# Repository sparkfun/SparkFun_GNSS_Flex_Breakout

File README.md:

SparkFun GNSS Flex Breakout
========================================

[*SparkFun GNSS Flex Breakout (GPS-28962)*](https://www.sparkfun.com/sparkfun-gnss-flex-breakout.html)

The [SparkFun GNSS Flex breakout](https://www.sparkfun.com/sparkfun-gnss-flex-breakout.html) is a *carrier board* for our GNSS Flex modules. In its simplest form, the GNSS Flex Breakout board provides access to all of the interfaces from a GNSS Flex module.

- Need access to all those UART pins? The Breakout provides that.
- Want to communicate with the GNSS directly over USB? You can do that too, if the GNSS module supports USB.

The GNSS Flex Breakout comes populated with two sets of 2x10 pin, 2mm pitch male headers for attaching a GNSS Flex module. With these headers, the GNSS Flex system is designed to be modular so that boards are pin-compatible for upgrades and can be easily swapped for repairs. Depending on the capabilities of the GNSS Flex module that is connected, these pins will breakout the USB, UART (x4), I^2^C, and SD card interfaces for the GNSS receiver along with any PPS (x2) or event (x2) signals, using a standardized pin out.

By default, the CH342 USB-to-Serial converter chip is connected to both the GNSS `UART1` and `UART2` interfaces. When you connect the `UART` USB port to your computer and install the driver, those two UART interfaces will appear as COM ports. If you need dedicated access to the `UART1` or `UART2` breakout pins, or want to use either of the JST connectors, you will need to disable the CH342. On this board, we have made this simple; just pull the `CH342 EN` breakout pin `LOW` or connect it to `GND`. Otherwise, there is also a `CH342 EN` jumper you can solder instead.

We have also included two 6-pin JST connectors, same as the ones used on Pixhawk flight controllers. The JST connectors allow you to: connect the GNSS to a Pixhawk; or connect a radio to the GNSS to transfer (e.g.) RTCM correction data. There are four LEDs indicators for power to the board and the `PPS1`, `PVT`, and `RTK` signals from the GNSS Flex module. Power can be provided by any or all of: the USB connectors or the `VIN` breakout pin. By default, Pin 1 of the JST connectors provides 5V output. But jumpers on the board allow the voltage to be changed to 3.3V. Or you can isolate the other power sources and connect an external 5V power input on Pin 1 instead. It is up to you.

> [!IMPORTANT]
> Depending on the GNSS Flex module, this product will likely require an external antenna:
>
> - Be sure to check out the hookup guide for more information on the GNSS Flex module.
> - Users can also find [GNSS Antennas](https://www.sparkfun.com/gnss/gnss-antennas.html) in our catalog.
>
> Users will have two options for connecting an external GNSS antenna to their GNSS receiver.
>
> - The GNSS Flex modules will usually come with a U.FL connector for external antenna.
> - For a sturdier connection, an SMA connector is available on the SparkFun GNSS Flex Breakout that is bridged to an U.FL connector. Users simply need to jumper the U.FL connectors on both the SparkPNT GNSS Flex module and SparkFun GNSS Flex Breakout with a short U.FL cable.

Documentation
--------------
- **[Hookup Guide (mkdocs)](http://docs.sparkfun.com/SparkFun_GNSS_Flex_System/)** - A hookup guide for the entire ecosystem of SparkFun GNSS Flex carrier boards and SparkPNT GNSS Flex modules, hosted by GitHub pages.<br>

Repository Contents
-------------------
- **[/docs](/docs/)** - Online documentation files
  - [/assets](/docs/assets/) - Assets files
    - [/3d_model](/docs/assets/3d_model/) - Files for the 3D models
      - [/3D CAD Model](/docs/assets/3d_model/cad_model.step) (.step)
    - [/board_files](/docs/assets/board_files/) - Files for the product design
      - [KiCad Design Files](/docs/assets/board_files/kicad_files.zip) (.zip)
      - [Schematic](/docs/assets/board_files/schematic.pdf) (.pdf)
      - [Dimensions](/docs/assets/board_files/dimensions.pdf) (.pdf)
    - [/component_documentation](/docs/assets/component_documentation/) - Datasheets for hardware components
    - [/img/hookup_guide/](/docs/assets/img/hookup_guide/) - Images for hookup guide documentation
- **[/Hardware](/Hardware/)** - Hardware design files (.brd, .sch)
  - **[/Production](/Production/)** - Production files

Product Variants
----------------
GNSS Flex *Carrier* Boards:

- [GPS-28962](https://www.sparkfun.com/sparkfun-gnss-flex-breakout.html) - GNSS Flex Breakout
- [GPS-28137](https://www.sparkfun.com/sparkfun-gnss-flex-phat.html) - GNSS Flex pHAT

Version History
---------------
- [v10](https://github.com/sparkfun/SparkFun_GNSS_Flex_Breakout/releases/tag/v10) - Initial Release
- [v11](https://github.com/sparkfun/SparkFun_GNSS_Flex_Breakout/releases/tag/v11) - Refactored the 3D model for new color adjustment script

License Information
-------------------

This product is ***open source***!

Please review the [`LICENSE.md`](./LICENSE.md) file for license information.

If you have any questions or concerns about licensing, please contact technical support on our [SparkFun forums](https://forum.sparkfun.com/viewforum.php?f=152).

Distributed as-is; no warranty is given.

- Your friends at SparkFun.

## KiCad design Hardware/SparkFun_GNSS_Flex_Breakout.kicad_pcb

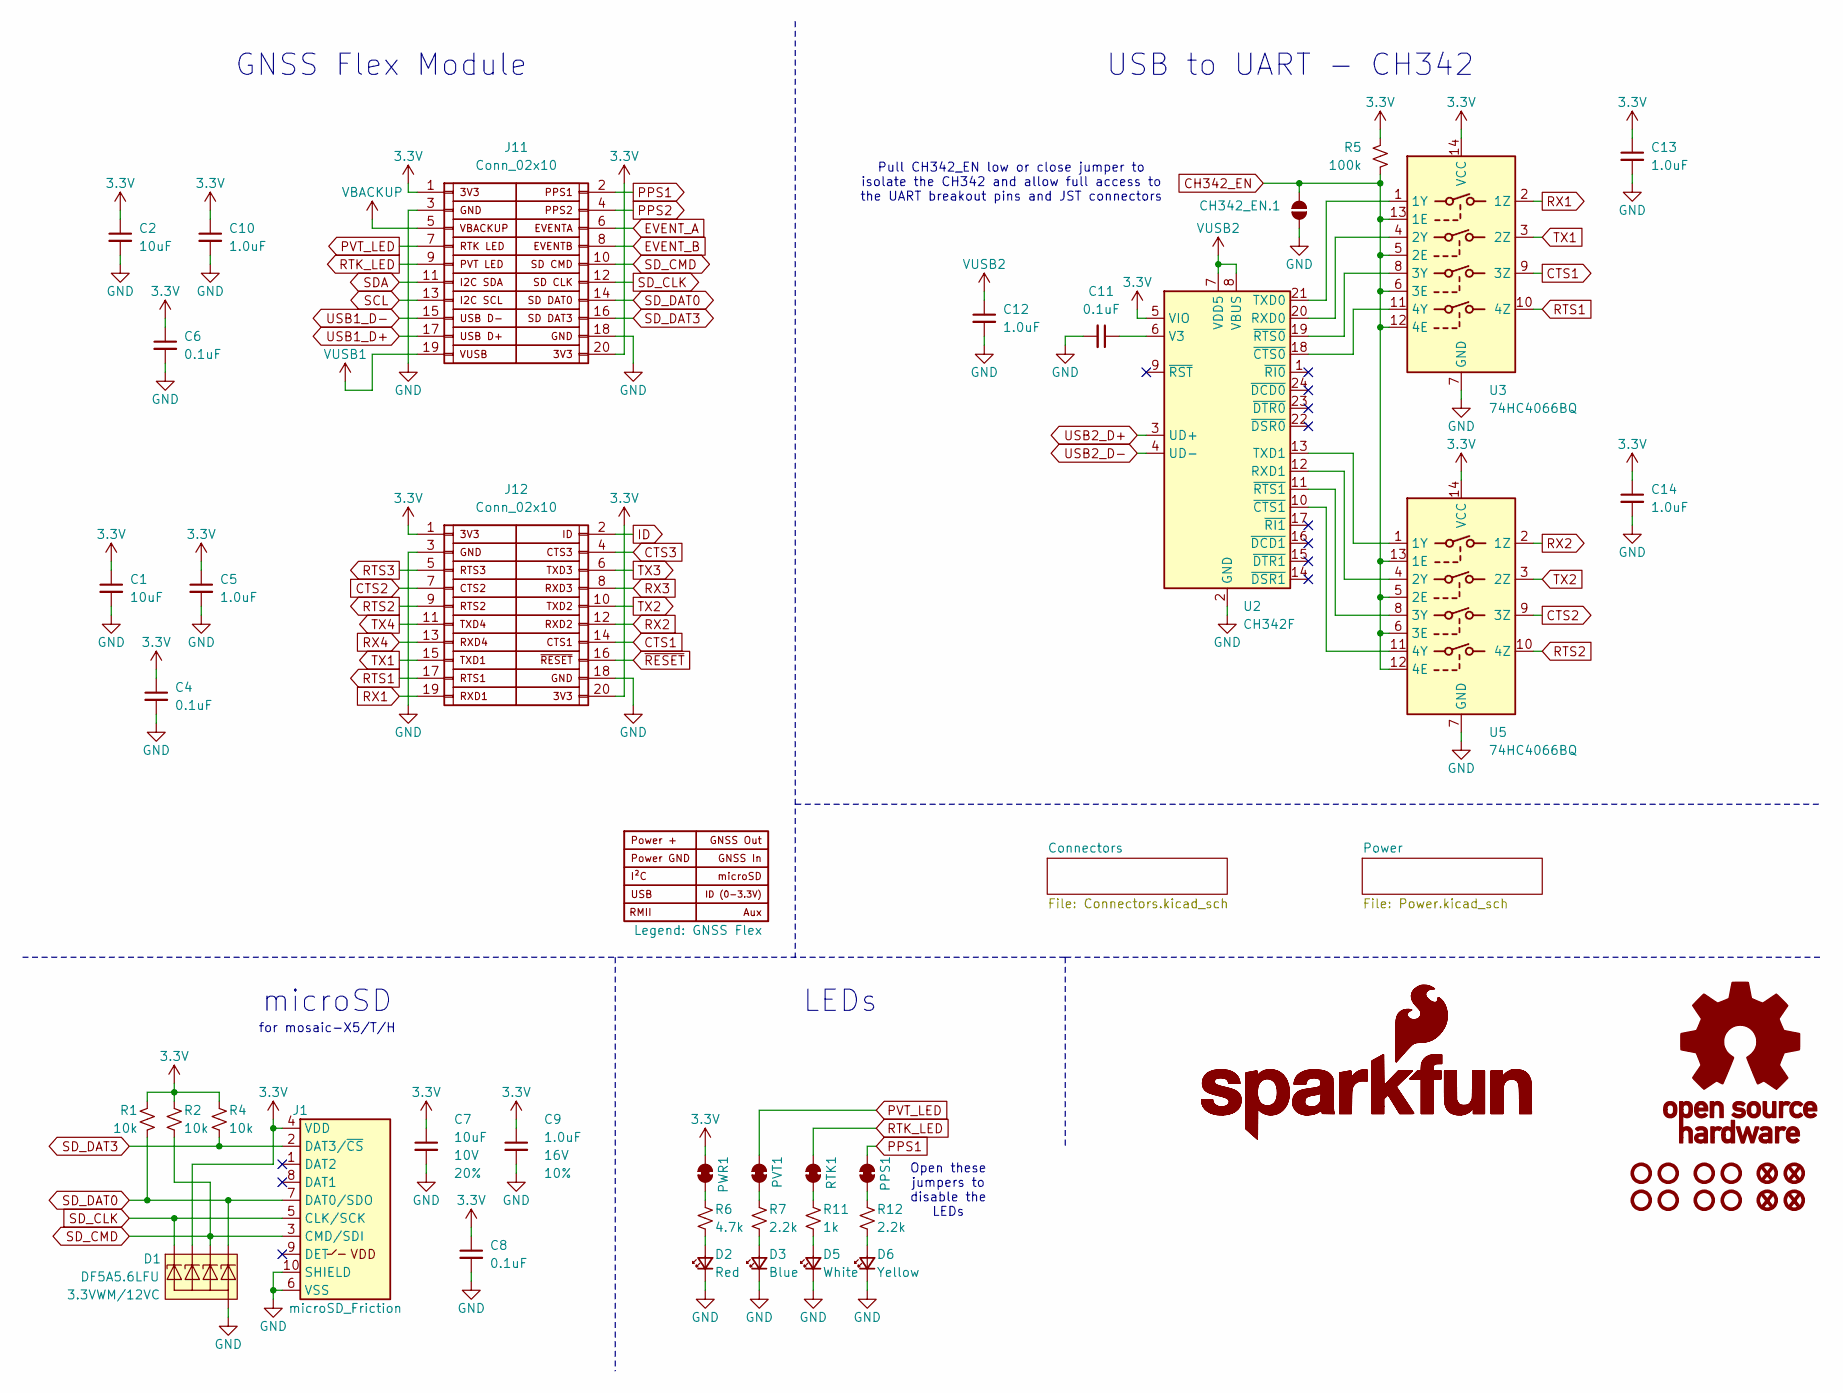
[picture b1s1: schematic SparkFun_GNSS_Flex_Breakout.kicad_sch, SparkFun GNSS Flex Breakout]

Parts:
C1, C2, C7: 10uF; C_0603_1608Metric; Voltage 10V; Tolerance 20%
C4, C6, C8, C11: 0.1uF; C_0603_1608Metric; Voltage 25V; Tolerance 20%
C5, C9, C10, C12, C13, C14: 1.0uF; C_0603_1608Metric; Voltage 16V; Tolerance 10%
CH342_EN.1: Jumper_2_NO
D1: DF5A5.6LFU; SOT-353; Rating 3.3VWM/12VC
D2: Red; LED_0603_1608Metric_Red
D3: Blue; LED_0603_1608Metric_Blue
D5: White; LED_0603_1608Metric_White
D6: Yellow; LED_0603_1608Metric_Yellow
FID1, FID2, FID3, FID4: Fiducial_0.5mm; Fiducial_0.5mm_Mask1mm
G1, G2: SparkFun_Logo
G3: OSHW_Logo; Creative_Commons_License
J1: microSD_Friction; microSD_Friction_Fit_Common
J11, J12: Conn_02x10; 2x10_2.0mm_Male_Pins_Vertical_SMD_Pegs
J15: Legend: GNSS Flex; GNSS_Flex_Template
PPS1: Jumper_2_NC_Trace
PVT1: Jumper_2_NC_Trace
PWR1: Jumper_2_NC_Trace
R1, R2, R4: 10k; R_0603_1608Metric
R5: 100k; R_0603_1608Metric
R6: 4.7k; R_0603_1608Metric
R7, R12: 2.2k; R_0603_1608Metric
R11: 1k; R_0603_1608Metric
RTK1: Jumper_2_NC_Trace
ST1, ST2, ST3, ST4, ST5, ST6, ST7, ST8: Standoff
U2: CH342F; QFN-24-1EP_4x4mm_P0.5mm_EP2.7x2.7mm
U3, U5: 74HC4066BQ; QFN-14_2.5x3mm_P0.5mm_EP1x1.5mm

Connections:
3.3V: C1.1, C2.1, C4.1, C5.1, C6.1, C7.1, C8.1, C9.1, C10.1, C13.1, C14.1, D1.3 (K2), J1.4 (VDD), J11.1, J11.20, J12.1, J12.20, PWR1.2 (B), R1.2, R2.2, R4.2, R5.2, U2.5 (VIO), U3.14 (VCC), U5.14 (VCC); also elsewhere on the board
CH342_EN: CH342_EN.1.2 (B), R5.1, U3.5 (2E), U3.6 (3E), U3.12 (4E), U3.13 (1E), U5.5 (2E), U5.6 (3E), U5.12 (4E), U5.13 (1E); also elsewhere on the board
CTS1: J12.14, U3.9 (3Z); also elsewhere on the board
CTS2: J12.7, U5.9 (3Z); also elsewhere on the board
CTS3: J12.4; also elsewhere on the board
EVENT_A: J11.6; also elsewhere on the board
EVENT_B: J11.8; also elsewhere on the board
GND: C1.2, C2.2, C4.2, C5.2, C6.2, C7.2, C8.2, C9.2, C10.2, C11.2, C12.2, C13.2, C14.2, CH342_EN.1.1 (A), D1.2 (A), D2.1 (K), D3.1 (K), D5.1 (K), D6.1 (K), J1.6 (VSS), J1.10 (SHIELD), J11.3, J11.18, J12.3, J12.18, U2.2 (GND), U2.25 (GND), U3.7 (GND), U5.7 (GND); also elsewhere on the board
ID: J12.2; also elsewhere on the board
unnamed: D2.2 (A), R6.1
unnamed: D3.2 (A), R7.1
unnamed: D5.2 (A), R11.1
unnamed: D6.2 (A), R12.1
unnamed: PPS1.1 (A), R12.2
unnamed: PVT1.1 (A), R7.2
unnamed: PWR1.1 (A), R6.2
unnamed: R11.2, RTK1.1 (A)
unnamed: U2.20 (RXD0), U3.4 (2Y)
unnamed: U2.12 (RXD1), U5.4 (2Y)
unnamed: U2.21 (TXD0), U3.1 (1Y)
unnamed: U2.13 (TXD1), U5.1 (1Y)
unnamed: C11.1, U2.6 (V3)
unnamed: U2.18 (~CTS0), U3.11 (4Y)
unnamed: U2.10 (~CTS1), U5.11 (4Y)
unnamed: U2.19 (~RTS0), U3.8 (3Y)
unnamed: U2.11 (~RTS1), U5.8 (3Y)
PPS1: J11.2, PPS1.2 (B); also elsewhere on the board
PPS2: J11.4; also elsewhere on the board
RTS1: J12.17, U3.10 (4Z); also elsewhere on the board
RTS2: J12.9, U5.10 (4Z); also elsewhere on the board
RTS3: J12.5; also elsewhere on the board
RX1: J12.19, U3.2 (1Z); also elsewhere on the board
RX2: J12.12, U5.2 (1Z); also elsewhere on the board
RX3: J12.8; also elsewhere on the board
RX4: J12.13; also elsewhere on the board
SCL: J11.13; also elsewhere on the board
SDA: J11.11; also elsewhere on the board
SD_CLK: D1.1 (K1), J1.5 (CLK/SCK), J11.12
SD_CMD: D1.4 (K3), J1.3 (CMD/SDI), J11.10, R2.1
SD_DAT0: D1.5 (K4), J1.7 (DAT0/SDO), J11.14, R1.1
SD_DAT3: J1.2 (DAT3/~CS), J11.16, R4.1
TX1: J12.15, U3.3 (2Z); also elsewhere on the board
TX2: J12.10, U5.3 (2Z); also elsewhere on the board
TX3: J12.6; also elsewhere on the board
TX4: J12.11; also elsewhere on the board
USB1_D+: J11.17; also elsewhere on the board
USB1_D-: J11.15; also elsewhere on the board
USB2_D+: U2.3 (UD+); also elsewhere on the board
USB2_D-: U2.4 (UD-); also elsewhere on the board
VBACKUP: J11.5; also elsewhere on the board
VUSB1: J11.19; also elsewhere on the board
VUSB2: C12.1, U2.7 (VDD5), U2.8 (VBUS); also elsewhere on the board
~RESET: J12.16; also elsewhere on the board

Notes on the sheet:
LEDs
USB to UART - CH342
GNSS Flex Module
for mosaic-X5/T/H
Open these jumpers to disable the LEDs
microSD
Pull CH342_EN low or close jumper to isolate the CH342 and allow full access to the UART breakout pins and JST connectors

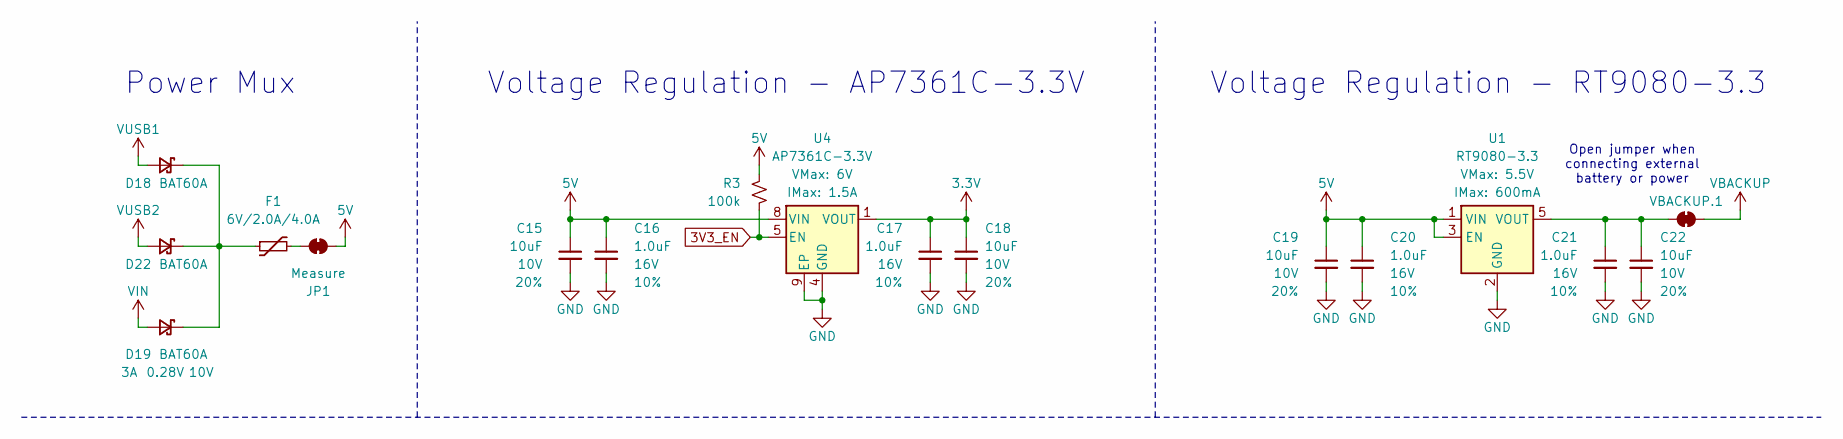
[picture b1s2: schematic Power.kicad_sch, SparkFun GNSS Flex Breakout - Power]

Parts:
C15, C18, C19, C22: 10uF; C_0603_1608Metric; Voltage 10V; Tolerance 20%
C16, C17, C20, C21: 1.0uF; C_0603_1608Metric; Voltage 16V; Tolerance 10%
D18, D19, D22: BAT60A; SOD-323
F1: 6V/2.0A/4.0A; 1210
JP1: Measure; Jumper_2_PTH_SMD_Combo-NC
R3: 100k; R_0603_1608Metric
U1: RT9080-3.3; SOT23-5
U4: AP7361C-3.3V; DFN-8_3x3mm
VBACKUP.1: Jumper_2_NC_Trace

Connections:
3.3V: C17.1, C18.1, U4.1 (VOUT); also elsewhere on the board
3V3_EN: R3.1, U4.5 (EN); also elsewhere on the board
5V: C15.1, C16.1, C19.1, C20.1, JP1.2 (B), R3.2, U1.1 (VIN), U1.3 (EN), U4.8 (VIN); also elsewhere on the board
GND: C15.2, C16.2, C17.2, C18.2, C19.2, C20.2, C21.2, C22.2, U1.2 (GND), U4.4 (GND), U4.9 (EP); also elsewhere on the board
unnamed: D18.1 (K), D19.1 (K), D22.1 (K), F1.1
unnamed: F1.2, JP1.1 (A)
unnamed: C21.1, C22.1, U1.5 (VOUT), VBACKUP.1.1 (A)
VBACKUP: VBACKUP.1.2 (B); also elsewhere on the board
VIN: D19.2 (A); also elsewhere on the board
VUSB1: D18.2 (A); also elsewhere on the board
VUSB2: D22.2 (A); also elsewhere on the board

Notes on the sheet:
Voltage Regulation - RT9080-3.3
Power Mux
Voltage Regulation - AP7361C-3.3V
Open jumper when connecting external battery or power

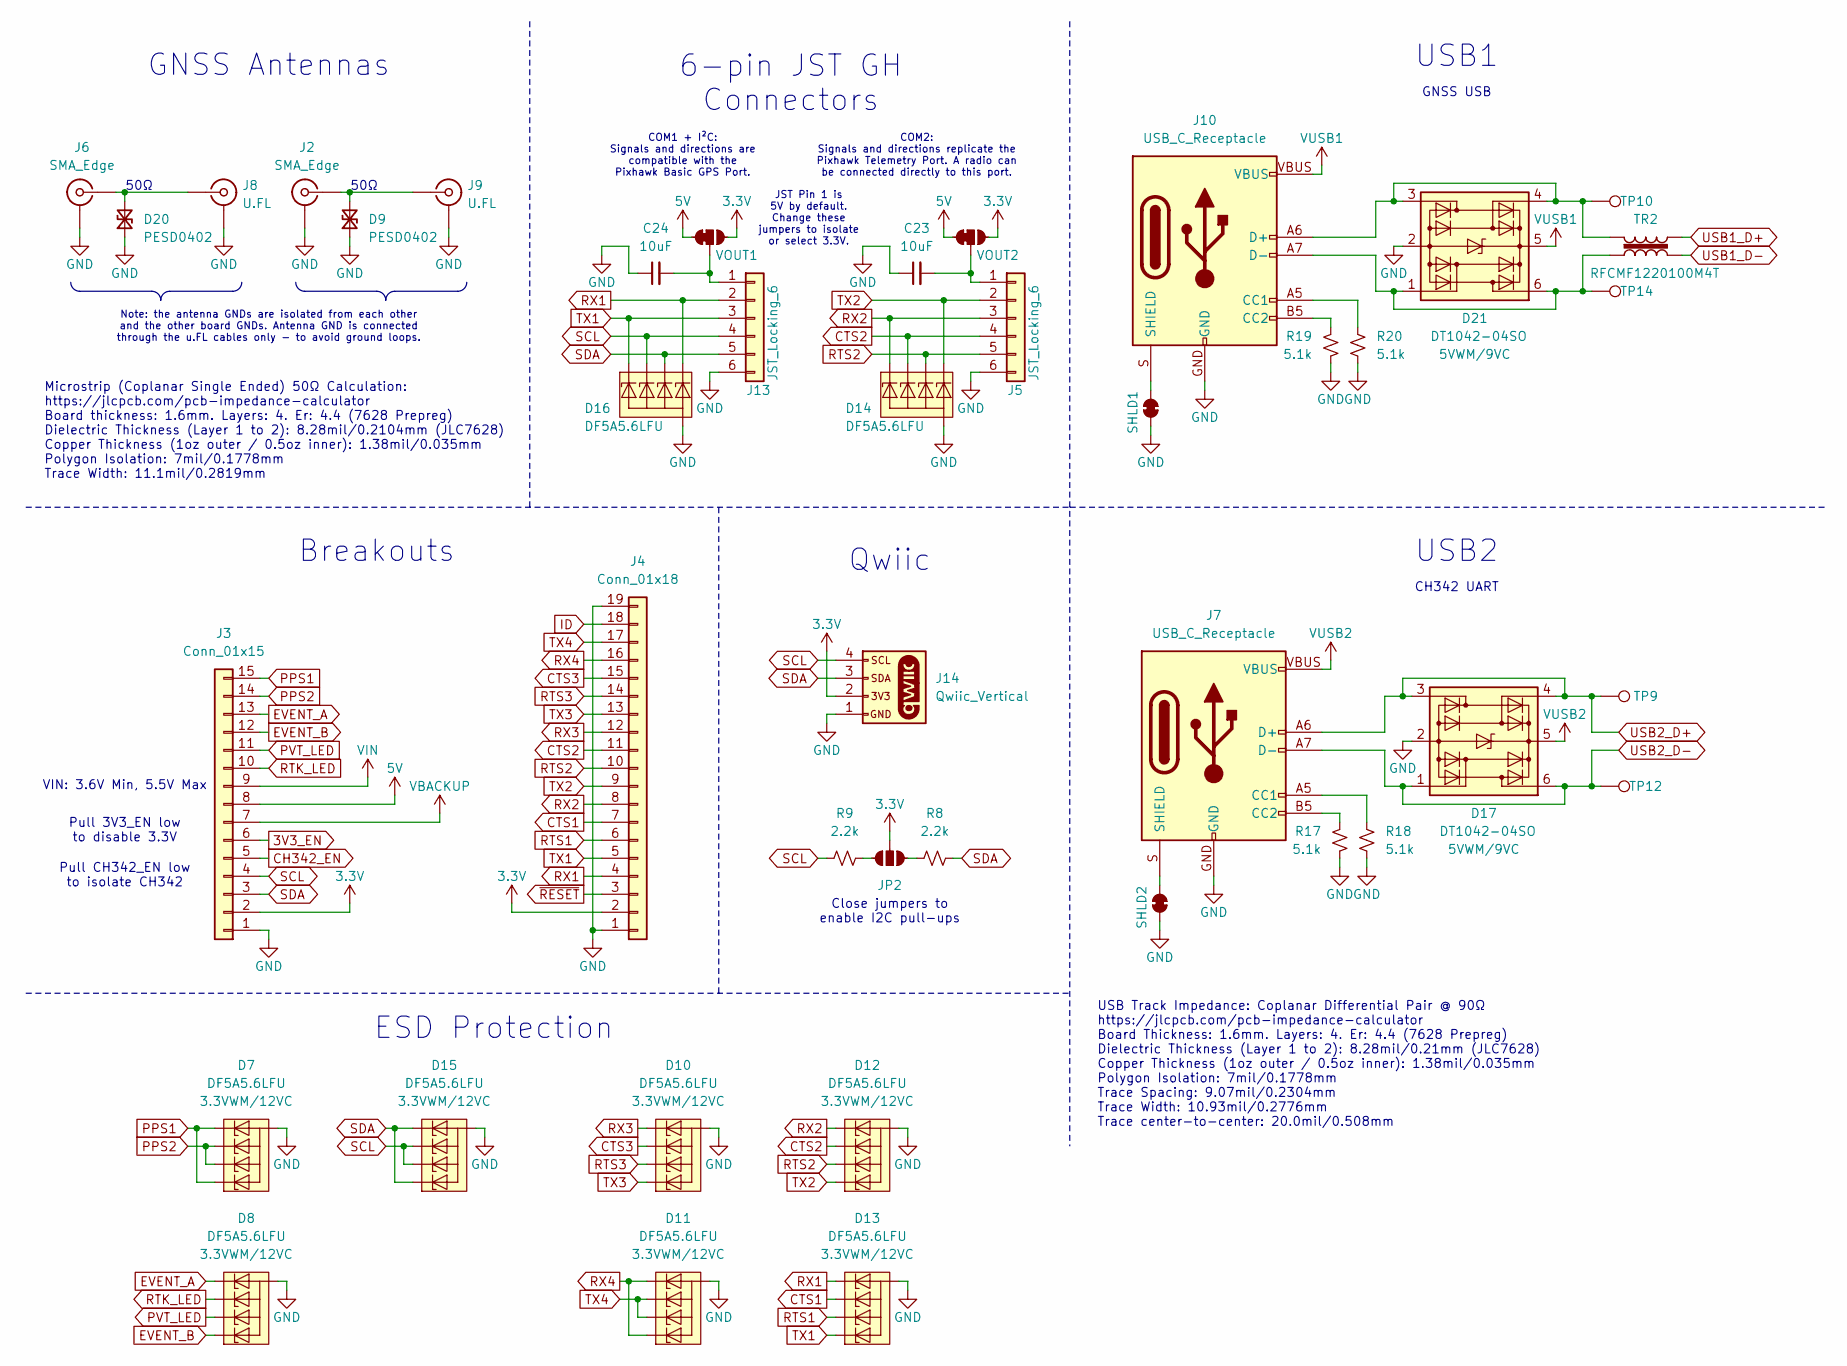
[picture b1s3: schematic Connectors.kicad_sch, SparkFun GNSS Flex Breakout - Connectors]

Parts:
C23, C24: 10uF; C_0603_1608Metric; Voltage 10V; Tolerance 20%
D7, D8, D10, D11, D12, D13, D14, D15, D16: DF5A5.6LFU; SOT-353; Rating 3.3VWM/12VC
D9, D20: PESD0402; C_0402_1005Metric; Rating 14VWM/40VC
D17, D21: DT1042-04SO; SOT23-6; Rating 5VWM/9VC
J2, J6: SMA_Edge
J3: Conn_01x15; 1x15
J4: Conn_01x18; 1x19
J5, J13: JST_Locking_6; JST_SMD_1.25mm-6_Locking
J7, J10: USB_C_Receptacle; USB-C_16
J8, J9: U.FL
J14: Qwiic_Vertical; JST_SMD_1.0mm-4_Vertical_Black
JP2: Jumper_3_NO
R8, R9: 2.2k; R_0603_1608Metric
R17, R18, R19, R20: 5.1k; R_0603_1608Metric
SHLD1, SHLD2: Jumper_2_NC_Trace
TP9, TP10, TP12, TP14: 1.25mm; TestPoint-1.25mm
TR2: RFCMF1220100M4T
VOUT1, VOUT2: Jumper_3_NC-1_Trace

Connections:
3.3V: J3.2, J4.2, J14.2, JP2.2 (B), VOUT1.3 (C), VOUT2.3 (C); also elsewhere on the board
3V3_EN: J3.6; also elsewhere on the board
5V: J3.8, VOUT1.1 (A), VOUT2.1 (A); also elsewhere on the board
CH342_EN: J3.5; also elsewhere on the board
CTS1: D13.4 (K3), J4.7; also elsewhere on the board
CTS2: D12.4 (K3), D14.3 (K2), J4.11, J5.4; also elsewhere on the board
CTS3: D10.4 (K3), J4.15; also elsewhere on the board
EVENT_A: D8.5 (K4), J3.13; also elsewhere on the board
EVENT_B: D8.1 (K1), J3.12; also elsewhere on the board
GND: C23.1, C24.1, D7.2 (A), D8.2 (A), D9.1 (A1), D10.2 (A), D11.2 (A), D12.2 (A), D13.2 (A), D14.2 (A), D15.2 (A), D16.2 (A), D17.2 (GND), D20.1 (A1), D21.2 (GND), J2.2 (Ext), J3.1, J4.1, J4.19, J5.6, J6.2 (Ext), J7.GND, J8.2 (Ext), J9.2 (Ext), J10.GND, J13.6, J14.1, R17.1, R18.1, R19.1, R20.1, SHLD1.1 (A), SHLD2.1 (A); also elsewhere on the board
ID: J4.18; also elsewhere on the board
unnamed: D9.2 (A2), J2.1 (In), J9.1 (In)
unnamed: D20.2 (A2), J6.1 (In), J8.1 (In)
unnamed: D21.1 (I/O1), D21.6 (I/O4), J10.A7 (D-), J10.B7 (D-), TP14.1, TR2.1
unnamed: D21.3 (I/O2), D21.4 (I/O3), J10.A6 (D+), J10.B6 (D+), TP10.1, TR2.3
unnamed: C23.2, J5.1, VOUT2.2 (B)
unnamed: J7.A5 (CC1), R18.2
unnamed: J7.B5 (CC2), R17.2
unnamed: J7.S (SHIELD), SHLD2.2 (B)
unnamed: J10.A5 (CC1), R20.2
unnamed: J10.B5 (CC2), R19.2
unnamed: J10.S (SHIELD), SHLD1.2 (B)
unnamed: C24.2, J13.1, VOUT1.2 (B)
unnamed: JP2.1 (A), R8.1
unnamed: JP2.3 (C), R9.2
PPS1: D7.1 (K1), D7.5 (K4), J3.15; also elsewhere on the board
PPS2: D7.3 (K2), D7.4 (K3), J3.14; also elsewhere on the board
RTS1: D13.3 (K2), J4.6; also elsewhere on the board
RTS2: D12.3 (K2), D14.4 (K3), J4.10, J5.5; also elsewhere on the board
RTS3: D10.3 (K2), J4.14; also elsewhere on the board
RX1: D13.5 (K4), D16.5 (K4), J4.4, J13.2; also elsewhere on the board
RX2: D12.5 (K4), D14.1 (K1), J4.8, J5.3; also elsewhere on the board
RX3: D10.5 (K4), J4.12; also elsewhere on the board
RX4: D11.1 (K1), D11.5 (K4), J4.16; also elsewhere on the board
SCL: D15.3 (K2), D15.4 (K3), D16.3 (K2), J3.4, J13.4, J14.4, R9.1; also elsewhere on the board
SDA: D15.1 (K1), D15.5 (K4), D16.4 (K3), J3.3, J13.5, J14.3, R8.2; also elsewhere on the board
TX1: D13.1 (K1), D16.1 (K1), J4.5, J13.3; also elsewhere on the board
TX2: D12.1 (K1), D14.5 (K4), J4.9, J5.2; also elsewhere on the board
TX3: D10.1 (K1), J4.13; also elsewhere on the board
TX4: D11.3 (K2), D11.4 (K3), J4.17; also elsewhere on the board
USB1_D+: TR2.4; also elsewhere on the board
USB1_D-: TR2.2; also elsewhere on the board
USB2_D+: D17.3 (I/O2), D17.4 (I/O3), J7.A6 (D+), J7.B6 (D+), TP9.1; also elsewhere on the board
USB2_D-: D17.1 (I/O1), D17.6 (I/O4), J7.A7 (D-), J7.B7 (D-), TP12.1; also elsewhere on the board
VBACKUP: J3.7; also elsewhere on the board
VIN: J3.9; also elsewhere on the board
VUSB1: D21.5 (VCC), J10.VBUS; also elsewhere on the board
VUSB2: D17.5 (VCC), J7.VBUS; also elsewhere on the board
~RESET: J4.3; also elsewhere on the board

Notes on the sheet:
Breakouts
USB1
USB Track Impedance: Coplanar Differential Pair @ 90Ω https://jlcpcb.com/pcb-impedance-calculator Board Thickness: 1.6mm. Layers: 4. Er: 4.4 (7628 Prepreg) Dielectric Thickness (Layer 1 to 2): 8.28mil/0.21mm (JLC7628) Copper Thickness (1oz outer / 0.5oz inner): 1.38mil/0.035mm Polygon Isolation: 7m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
50Ω
Close jumpers to enable I2C pull-ups
CH342 UART
COM1 + I²C: Signals and directions are compatible with the Pixhawk Basic GPS Port.
Pull 3V3_EN low to disable 3.3V
GNSS Antennas
JST Pin 1 is 5V by default. Change these jumpers to isolate or select 3.3V.
GNSS USB
COM2: Signals and directions replicate the Pixhawk Telemetry Port. A radio can be connected directly to this port.
Pull CH342_EN low to isolate CH342
USB2
Microstrip (Coplanar Single Ended) 50Ω Calculation: https://jlcpcb.com/pcb-impedance-calculator Board thickness: 1.6mm. Layers: 4. Er: 4.4 (7628 Prepreg) Dielectric Thickness (Layer 1 to 2): 8.28mil/0.2104mm (JLC7628) Copper Thickness (1oz outer / 0.5oz inner): 1.38mil/0.035mm Polygon Isolation: 7m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
Note: the antenna GNDs are isolated from each other and the other board GNDs. Antenna GND is connected through the u.FL cables only - to avoid ground loops.
6-pin JST GH Connectors
ESD Protection
VIN: 3.6V Min, 5.5V Max
Qwiic

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
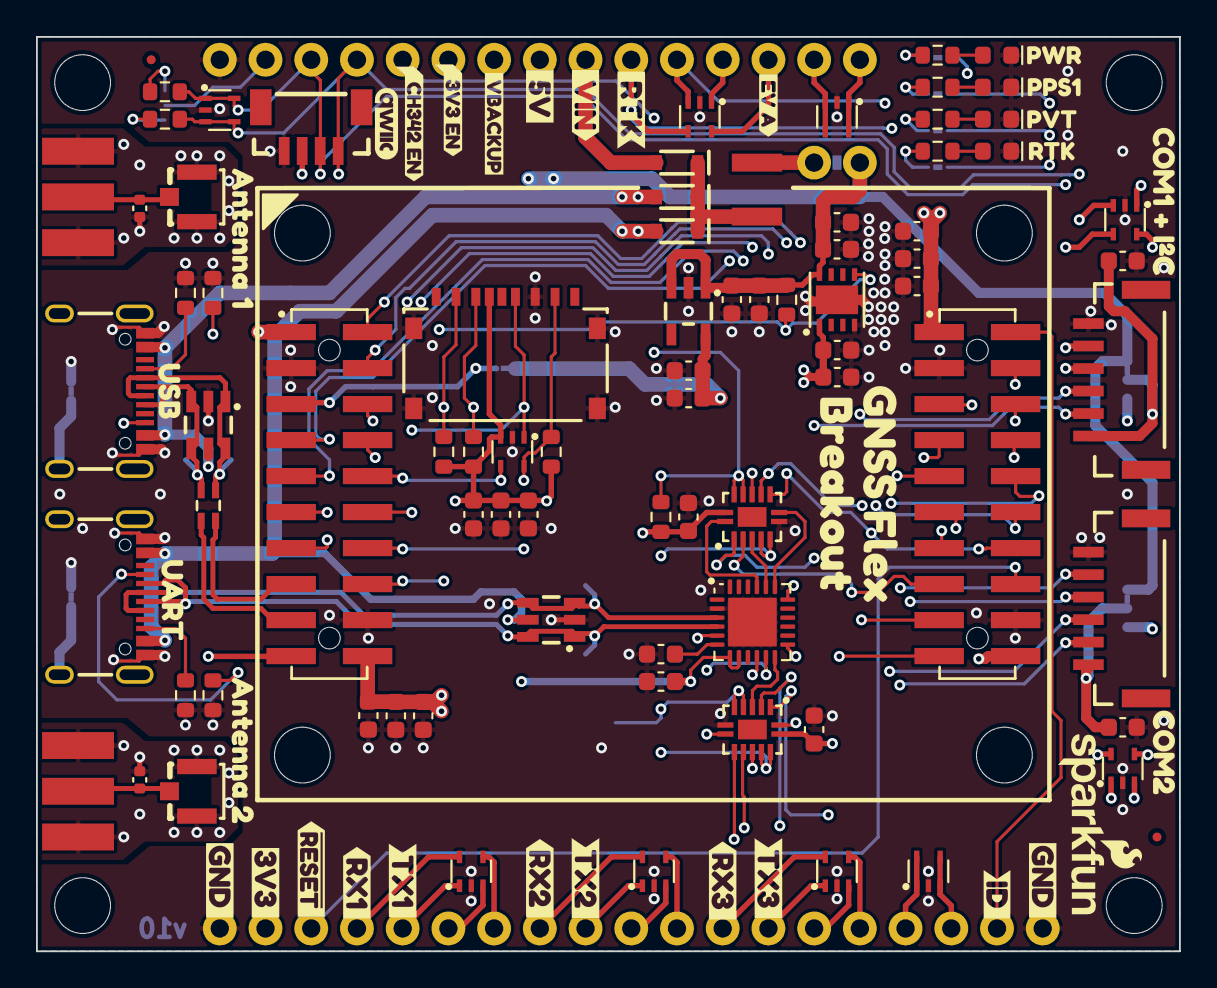
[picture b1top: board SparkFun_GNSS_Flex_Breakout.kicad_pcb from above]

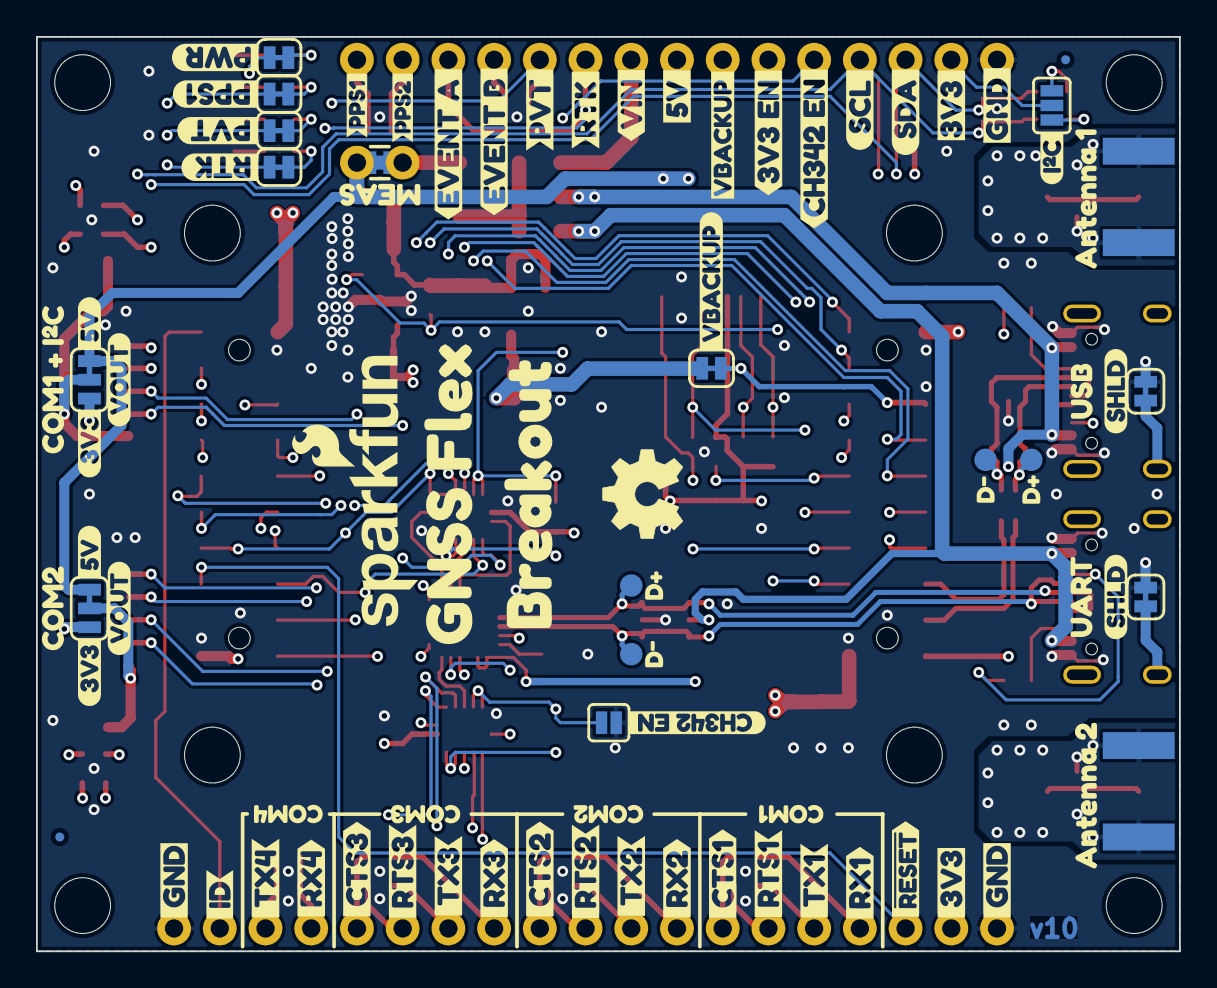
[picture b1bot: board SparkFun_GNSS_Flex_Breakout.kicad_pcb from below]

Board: 4 copper layers, 63.5 x 50.8 mm, 207 parts (85 on the bottom side), 75 nets.

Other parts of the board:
Ref**: Val**; OSHW_Logo_5mm
kibuzzard-67D04D07: G***; kibuzzard-67D04D07
kibuzzard-67D04D20: G***; kibuzzard-67D04D20
kibuzzard-67D04D30: G***; kibuzzard-67D04D30
kibuzzard-67D04E88: G***; kibuzzard-67D04E88
kibuzzard-67D022A2: G***; kibuzzard-67D022A2
kibuzzard-67D022AC: G***; kibuzzard-67D022AC
kibuzzard-67D044ED, kibuzzard-67D044ED#2: G***; kibuzzard-67D044ED
kibuzzard-67D045AD, kibuzzard-67D045AD#2: G***; kibuzzard-67D045AD
kibuzzard-67D045C9: G***; kibuzzard-67D045C9
kibuzzard-67D045EC: G***; kibuzzard-67D045EC
kibuzzard-67D046A8: G***; kibuzzard-67D046A8
kibuzzard-67D046B5: G***; kibuzzard-67D046B5
kibuzzard-67D046BD: G***; kibuzzard-67D046BD
kibuzzard-67D046CC: G***; kibuzzard-67D046CC
kibuzzard-67D046F7: G***; kibuzzard-67D046F7
kibuzzard-67D046FF: G***; kibuzzard-67D046FF
kibuzzard-67D171AB, kibuzzard-67D171AB#2: G***; kibuzzard-67D171AB
kibuzzard-67D171E5, kibuzzard-67D171E5#2: G***; kibuzzard-67D171E5
kibuzzard-67D1674C: G***; kibuzzard-67D1674C
kibuzzard-67D02274: G***; kibuzzard-67D02274
kibuzzard-67D03584: G***; kibuzzard-67D03584
kibuzzard-67D04501: G***; kibuzzard-67D04501
kibuzzard-67D04612: G***; kibuzzard-67D04612
kibuzzard-67D04639: G***; kibuzzard-67D04639
kibuzzard-67D04669: G***; kibuzzard-67D04669
kibuzzard-67D05112, kibuzzard-67D05112#2: G***; kibuzzard-67D05112
kibuzzard-67D16775: G***; kibuzzard-67D16775
kibuzzard-67DAC0B5, kibuzzard-67DAC0B5#2: G***; kibuzzard-67DAC0B5
kibuzzard-67E6AD3C, kibuzzard-67E6AD3C#2: G***; kibuzzard-67E6AD3C
kibuzzard-67E6AD12, kibuzzard-67E6AD12#2: G***; kibuzzard-67E6AD12
kibuzzard-67E6B1CF, kibuzzard-67E6B1CF#2: G***; kibuzzard-67E6B1CF
kibuzzard-67E6B1E0, kibuzzard-67E6B1E0#2: G***; kibuzzard-67E6B1E0
kibuzzard-67E6B4F7: G***; kibuzzard-67E6B4F7
kibuzzard-67E6B5D1: G***; kibuzzard-67E6B5D1
kibuzzard-67E6B5D6: G***; kibuzzard-67E6B5D6
kibuzzard-67E6B5E0: G***; kibuzzard-67E6B5E0
kibuzzard-67E6B5E7: G***; kibuzzard-67E6B5E7
kibuzzard-67E6B70A: G***; kibuzzard-67E6B70A
kibuzzard-67E6B547: G***; kibuzzard-67E6B547
kibuzzard-67E6B575: G***; kibuzzard-67E6B575
kibuzzard-67E6B720: G***; kibuzzard-67E6B720
kibuzzard-67E6B983: G***; kibuzzard-67E6B983
kibuzzard-67E6BA59: G***; kibuzzard-67E6BA59
kibuzzard-67E6BA73: G***; kibuzzard-67E6BA73
kibuzzard-67E6BA93: G***; kibuzzard-67E6BA93
kibuzzard-67E6BABA: G***; kibuzzard-67E6BABA
kibuzzard-67E6BAD6: G***; kibuzzard-67E6BAD6
kibuzzard-67E6BB49: G***; kibuzzard-67E6BB49
kibuzzard-67E6BB64: G***; kibuzzard-67E6BB64
kibuzzard-67E6BBAF: G***; kibuzzard-67E6BBAF
kibuzzard-67E6BBC6: G***; kibuzzard-67E6BBC6
kibuzzard-67E6C8C9: G***; kibuzzard-67E6C8C9
kibuzzard-67E6C8CF: G***; kibuzzard-67E6C8CF
kibuzzard-67E6C641: G***; kibuzzard-67E6C641
kibuzzard-67E68AA4: G***; kibuzzard-67E68AA4
kibuzzard-67E68AF7: G***; kibuzzard-67E68AF7
kibuzzard-67E68BE1: G***; kibuzzard-67E68BE1
kibuzzard-67E686E5: G***; kibuzzard-67E686E5
kibuzzard-67E688B9: G***; kibuzzard-67E688B9
kibuzzard-67E688C1: G***; kibuzzard-67E688C1
kibuzzard-67E688C9: G***; kibuzzard-67E688C9
kibuzzard-67E688D0: G***; kibuzzard-67E688D0
kibuzzard-67E689B5: G***; kibuzzard-67E689B5
kibuzzard-67E689EA: G***; kibuzzard-67E689EA
kibuzzard-67E68821: G***; kibuzzard-67E68821
kibuzzard-67EE9EE3, kibuzzard-67EE9EE3#2: G***; kibuzzard-67EE9EE3
kibuzzard-67EE9EFF, kibuzzard-67EE9EFF#2: G***; kibuzzard-67EE9EFF
kibuzzard-67EEB40C: G***; kibuzzard-67EEB40C
kibuzzard-67EEB400: G***; kibuzzard-67EEB400
kibuzzard-67EFA2E8: G***; kibuzzard-67EFA2E8
kibuzzard-67EFA2F1: G***; kibuzzard-67EFA2F1
kibuzzard-67EFDE56: G***; kibuzzard-67EFDE56
kibuzzard-67EFEB6F: G***; kibuzzard-67EFEB6F
kibuzzard-67EFEB92: G***; kibuzzard-67EFEB92
kibuzzard-67F7B6D7: G***; kibuzzard-67F7B6D7
kibuzzard-67F7B700: G***; kibuzzard-67F7B700
kibuzzard-67F7C8FB: G***; kibuzzard-67F7C8FB
kibuzzard-67F7C94B: G***; kibuzzard-67F7C94B
kibuzzard-67F7C97D: G***; kibuzzard-67F7C97D
kibuzzard-67F7C969: G***; kibuzzard-67F7C969
kibuzzard-67F7C991: G***; kibuzzard-67F7C991
kibuzzard-682202FA: G***; kibuzzard-682202FA
kibuzzard-6822032F: G***; kibuzzard-6822032F
kibuzzard-68220336: G***; kibuzzard-68220336

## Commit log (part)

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2025-03-28 Add Hardware - ready for airwire review
2025-03-29 Update QFN-14 3D model. Nudge USB connectors
2025-04-03 Routing WIP
2025-04-04 Routed and panelized
2025-04-10 Updates after proto review
2025-04-22 PCB v02 - with corrected regulator footprint
2025-05-12 v10 PCB - correct PVT and RTK LEDs, and VBACKUP silk
2025-06-18 Remove folders
2025-06-18 Update LICENSE.md
    Remove line wrap
2025-06-24 Add banner images
2025-06-24 Move files
2025-09-18 Docs - Initial Draft
2025-10-10 Update 3D model
    Refactored the 3D model for all the GNSS Flex boards to a new standardization
    Eliminated the manual adjustments required for any new 3D models
    - Modified the old models, so any new models can be adopted without any changes after they have been optimized
2025-10-10 Update README.md
    Added v11 to the version history, noting the refactored 3D model for new color adjustment script.
2025-10-10 Add poster.png
    Adds poster image for the 3D model
2025-10-10 Update software_overview.md
    Replace snippet; redirect link fails
    Add icons to titles
2026-02-25 Docs - Tech Assist Update
    Removed links to technical assistance webpage (404 retail site)
    - Removed or relocated???

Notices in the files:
parts and their libraries:
https://creativecommons.org/licenses/by-sa/4.0
Released under the Creative Commons Attribution Share-Alike 4.0 License
